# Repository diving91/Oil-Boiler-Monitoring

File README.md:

# Oil-Boiler-Monitoring
MySensors sketch to Monitor an oil fired boiler &amp; Tune boiler water temperature based on External temperature provided by Mysensors controller

Fuel Sensor V2.0 - Diving91 - 2016 <br>
Mysensors Library used	: 2.0.0-beta<br>
Repeater Mode		: NO<br>
Power Supply		: From Mains, No Battery<br>
HW type			: Arduino Pro Mini 3.3V 8MHz<br>
Node Name		: Fuel Sensor<br> 
Purpose			: Monitoring of an oil fired boiler & Tune boiler water temperature based on External temperature provided by the controller<br>
<br>
<b>Description</b><br>
When boiler starts, Fuel Valve ON info is sent to the controller and time counter is started. A LED_PIN is set to HIGH
<br>
When Boiler stops,<br>
	- LED_PIN is set to LOW<br>
	- Fuel Valve OFF info is sent to the controller<br>
	- Fuel volume is computed, stored to EEPROM (in milli liters) in a circular buffer and sent to the controller (in liters)<br>
	- Sketch requests External temperature value to the controller, and compare it to HighTemp, LowTemp threshold values, and set RELAY_PIN based on this comparison<br>
<br>
The controller can perform 3 actions<br>
 	- Reset Fuel volume: The sketch will set volume to 0, request UTC time and send back LOCALE (GMT+1 Europe DST) time to the controller<br>
	- Set HighTemp threshold: The sketch stores it in EEPROM and send it back to controller<br>
	- Set LowTemp threshold: The sketch stores it in EEPROM and send it back to controller<br>
<br>
The RELAY_PIN is used to set boiler water temperature to 2 predetermined values (depends on your boiler characteritics)<br>
Eg: When External temperature > 5.0°C, boiler water temperature of 65°C is enough<br>
Eg: When External temperature < -1.0°C, boiler water temperature of 70°C or 72°C is better<br>
<br>
<b>Usage</b><br>
* 	When starting the node, take care the boiler is OFF as this is what the sketch assumes<br>
*	Fuel Boiler valve is ON when VALVE_PIN is LOW<br>
*	Boiler Temperature HIGH when RELAY_PIN is LOW<br>
*	Before first usage, erase EEPROM with 0xFF<br>
* 	At first usage Reset Fuel volume Counter and Send HighTemp & LowTemp Values<br>
*	At power on or after reset, Relay is set for LowTemp mode ie Summer conditions<br>
*	At power on or after reset, the sketch sends to controller stored values for Fuel Volume, HighTemp, LowTemp, so that the controller is initialized<br>
*	A DBG_PIN is used to determine at power on, if sketch debug information has to be sent on serial console or not
*	debug info from MySensors are controller at sketch compile time, not during run time<br>

<b>V2.0 Addition :</b><br>
*	Add ability to send volume in its seconds equivalent to let Controllers do the conversion when desired
* 	Add some wait() during presentation for better reliability 
*	Some bug fixes
*	Add 1-wire DS18B20 sensors reading and sending to Mysensors - Values are sent every custom defined time with & without redundancy
*	To be used with 2 sensors to monitor Water temperature out & in from the water path
*	When returning water temperature is too high, this indicates your Boiler water temperature might be too high
*	If no DS18B20 devices are attached, info is not presented to Mysensors controller

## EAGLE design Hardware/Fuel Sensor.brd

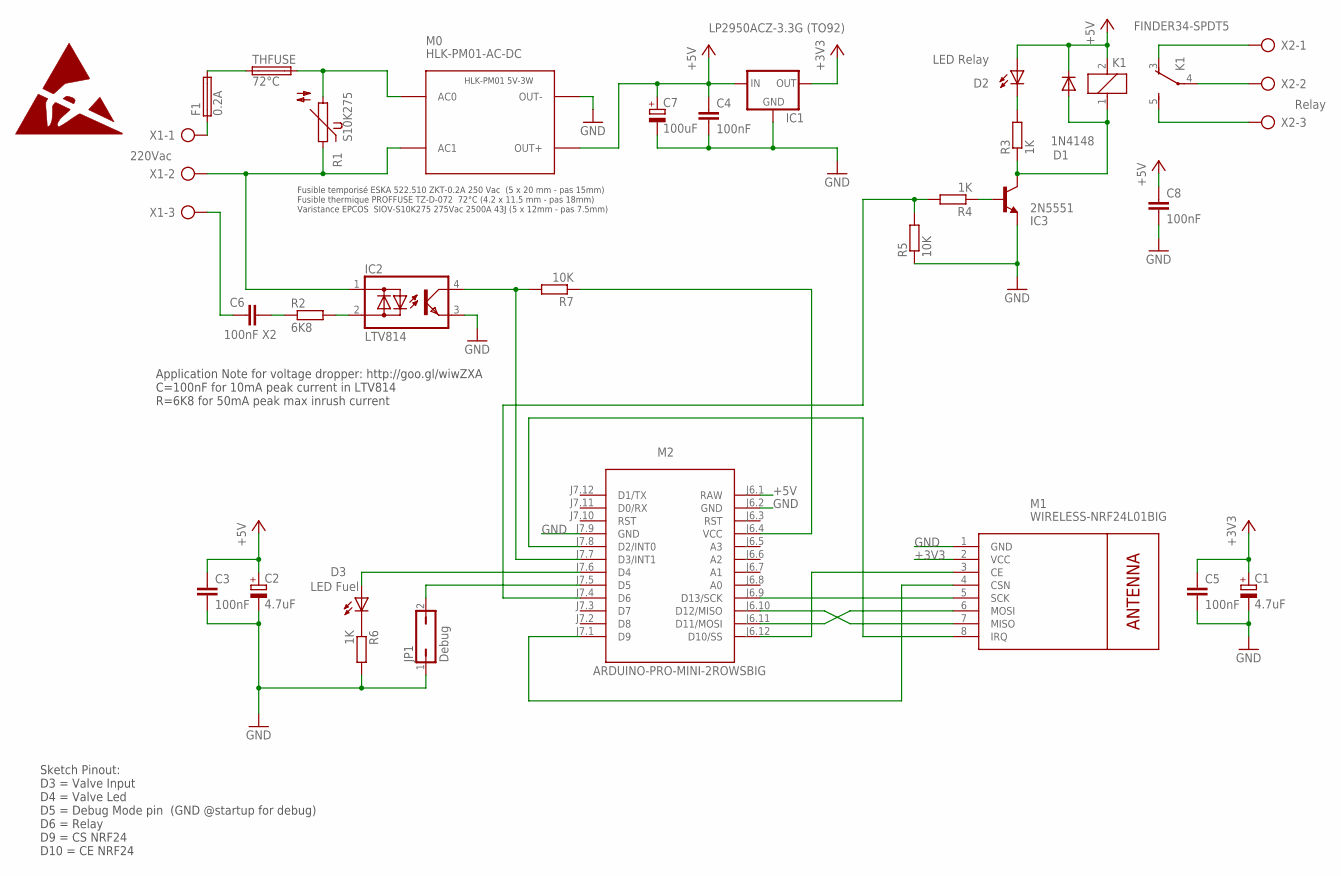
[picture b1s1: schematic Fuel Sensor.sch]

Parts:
C1, C2: 4.7uF; E2-5
C3, C4, C5, C8: 100nF; C-C320
C6: 100nF X2; C-B32922-MKPX2
C7: 100uF; E3-8
D1: 1N4148; DO35
D2: LED Relay; LED5MM
D3: LED Fuel; LED5MM
F1: 0.2A; PTF75
IC1: LP2950ACZ-3.3G (TO92); DC-DC-TO92L
IC2: LTV814; DIL04
IC3: 2N5551; T-T092L
JP1: Debug; JUMPER2
K1: FINDER34-SPDT5; FINDER34-SPDT
M0: HLK-PM01-AC-DC
M1: WIRELESS-NRF24L01BIG; WIRELESS-NRF24L01-DIY
M2: ARDUINO-PRO-MINI-2ROWSBIG; ARDUINO-PRO-MINI-2ROWS-DIY
R1: S10K275
R2: 6K8; PMR02S
R3, R4, R6: 1K; PMR0.25W
R5, R7: 10K; PMR0.25W
THFUSE: 72°C; PROFFUSE-TZ-D
X1: 220Vac; DG301-5.0-3
X2: Relay; DG301-5.0-3

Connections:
+3V3: C1.+, C5.1, IC1.OUT, M1.2 (VCC)
+5V: C2.+, C3.1, C4.1, C7.+, C8.1, D1.C, D2.A, IC1.IN, K1.2, M0.OUT+, M2.J6.1 (RAW)
GND: C1.-, C2.-, C3.2, C4.2, C5.2, C7.-, C8.2, IC1.GND, IC2.3 (E), IC3.E, JP1.1, M0.OUT-, M1.1 (GND), M2.J6.2 (GND), M2.J7.9 (GND), R5.1, R6.2
LINE: F1.1, X1.1
LINE1: F1.2, THFUSE.1
unnamed: D2.K (C), R3.2
unnamed: M1.8 (IRQ), M2.J7.8 (D2/INT0)
unnamed: D1.A, IC3.C, K1.1, R3.1
unnamed: M0.AC0, R1.2, THFUSE.2
unnamed: M1.7 (MISO), M2.J6.10 (D12/MISO)
unnamed: M1.6 (MOSI), M2.J6.11 (D11/MOSI)
unnamed: M1.4 (CSN), M2.J7.1 (D9)
unnamed: M1.5 (SCK), M2.J6.9 (D13/SCK)
unnamed: M1.3 (CE), M2.J6.12 (D10/SS)
unnamed: JP1.2, M2.J7.5 (D5)
unnamed: D3.A, M2.J7.6 (D4)
unnamed: M2.J7.4 (D6), R4.2, R5.2
unnamed: IC2.4 (C), M2.J7.7 (D3/INT1), R7.2
unnamed: M2.J6.4 (VCC), R7.1
unnamed: D3.K (C), R6.1
unnamed: C6.2, R2.1
unnamed: IC2.2 (AC2), R2.2
unnamed: IC3.B, R4.1
NEUTRAL: IC2.1 (AC1), M0.AC1, R1.1, X1.2
RC: K1.4, X2.2
ROFF: K1.3 (O), X2.1
RON: K1.5 (S), X2.3
VALVE: C6.1, X1.3

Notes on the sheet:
Fusible temporisé ESKA 522.510 ZKT-0.2A 250 Vac (5 x 20 mm - pas 15mm) Fusible thermique PROFFUSE TZ-D-072 72°C (4.2 x 11.5 mm - pas 18mm) Varistance EPCOS SIOV-S10K275 275Vac 2500A 43J (5 x 12mm - pas 7.5mm)
Sketch Pinout: D3 = Valve Input D4 = Valve Led D5 = Debug Mode pin (GND @startup for debug) D6 = Relay D9 = CS NRF24 D10 = CE NRF24
Application Note for voltage dropper: http://goo.gl/wiwZXA C=100nF for 10mA peak current in LTV814 R=6K8 for 50mA peak max inrush current

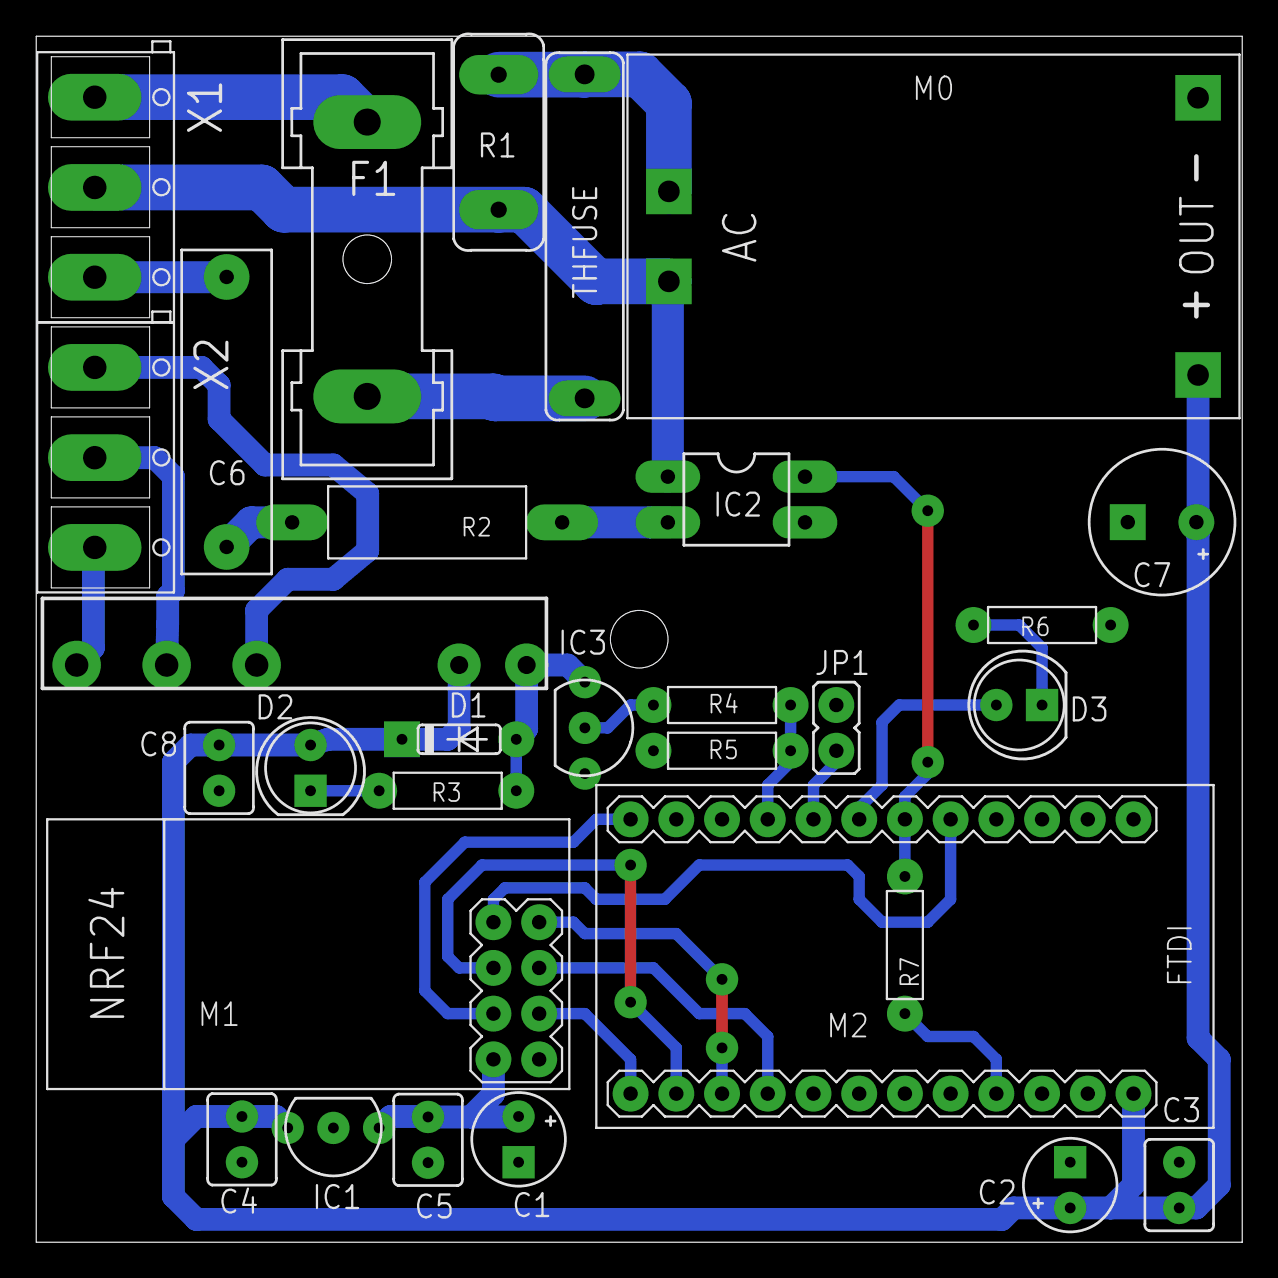
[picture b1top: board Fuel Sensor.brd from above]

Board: 2 copper layers, 67.0 x 67.0 mm, 31 parts (0 on the bottom side), 28 nets.

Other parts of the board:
DRILEGEND: DRILEGEND

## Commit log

2016-04-03 Added files via upload
2016-04-03 Create toto
2016-04-03 Create todo
2016-04-27 Add D3 input scope measurement
2016-04-28 Jeedom Widget
2016-04-28 PCB Layout
2016-04-28 PCB Copper side
2016-04-28 Eagle 7.5.0 design files & copper layer
2016-04-28 Cleanup
2016-05-06 Fix Resistor values for LEDs
2016-05-08 Picture of the PCB
2016-05-08 Picture of the board in its enclosure
2016-05-15 Add sketch V2 screen
2016-05-15 Update Readme for V2.0 additions
2016-05-15 Add V2.0 arduino sketch

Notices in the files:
parts and their libraries:
SparkFun-Aesthetics: Licensing: Creative Commons ShareAlike 4.0 International - https://creativecommons.org/licenses/by-sa/4.0
